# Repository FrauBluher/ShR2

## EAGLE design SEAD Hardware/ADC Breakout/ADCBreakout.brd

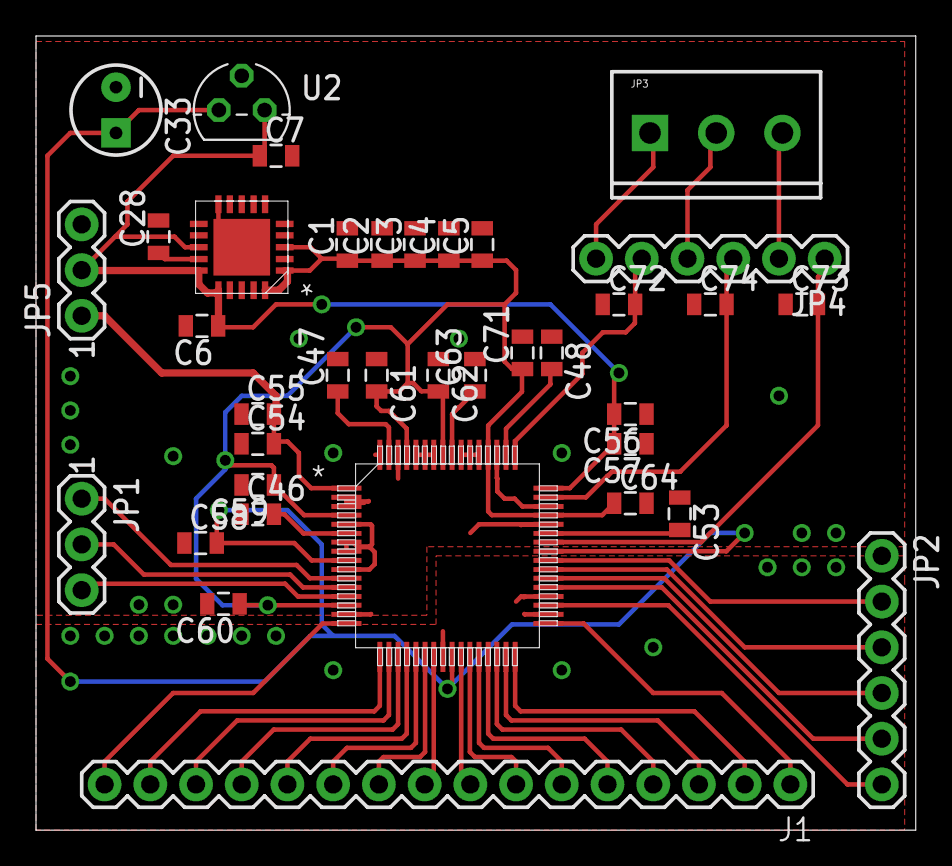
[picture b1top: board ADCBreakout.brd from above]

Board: 2 copper layers, 48.9 x 44.1 mm, 37 parts (0 on the bottom side), 41 nets.

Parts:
C1, C2, C3, C4, C5, C6, C7, C46, C47, C48, C53, C54, C56: 10uF; 0805
C28, C58: 1uF; 0805
C33: 10uF; CPOL-RADIAL-10UF-25V
C55, C57, C59, C60, C61, C62, C64, C71: .1uF; 0805
C63: .47uF; 0805
C72, C73, C74: 10nF; 0805
J1: M16PTH; 1X16
JP1, JP5: M03PTH; 1X03
JP2, JP4: 1X06
JP3: M03SCREW_LOCK; SCREWTERMINAL-3.5MM-3_LOCK.007S
U1: ADS8568_PM_64; PM64
U2: LP2950-3.3ACZ; TO92
U$3: TPS7A4700_RGW_20; RGW20_3P15X3P15

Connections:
AA1_R_OUT: C73.2, JP4.1, U1.42
AA2_R_OUT: C74.2, JP4.3, U1.47
AA3_R_OUT: C72.2, JP4.5, U1.49
ADC_DB0: J1.1, U1.33
ADC_DB1: J1.2, U1.32
ADC_DB2: J1.3, U1.31
ADC_DB3: J1.4, U1.30
ADC_DB4: J1.5, U1.29
ADC_DB5: J1.6, U1.28
ADC_DB6: J1.7, U1.27
ADC_DB7: J1.8, U1.26
ADC_DB8: J1.9, U1.23
ADC_DB9: J1.10, U1.22
ADC_DB10: J1.11, U1.21
ADC_DB11: J1.12, U1.20
ADC_DB12: J1.13, U1.19
ADC_DB13: J1.14, U1.18
ADC_DB14: J1.15, U1.17
ADC_DB15: J1.16, U1.16
BUSY: JP2.6, U1.35
CONV_A: JP2.5, U1.37
CONV_B: JP2.4, U1.38
CONV_C: JP2.3, U1.39
CONV_D: JP2.2, U1.40
CS*: JP1.3, U1.13
GND: C1.2, C2.2, C3.2, C4.2, C5.2, C6.2, C7.2, C28.2, C33.2, C46.1, C47.2, C48.1, C53.1, C54.1, C55.1, C56.1, C57.1, C58.1, C59.2, C60.2, C61.1, C62.1, C63.2, C64.2, C71.2, C72.1, C73.1, C74.1, JP2.1, JP5.3, U1.2, U1.3, U1.5, U1.7, U1.8, U1.10, U1.15, U1.24, U1.34, U1.36, U1.44, U1.46, U1.51, U1.53, U1.54, U1.55, U1.58, U1.59, U1.60, U1.62, U1.64, U2.2, U$3.6, U$3.7, U$3.10, U$3.21
HVDD_12A: C6.1, C7.1, C56.2, C57.2, JP5.2, U1.48, U2.3, U$3.13, U$3.15, U$3.16
HVSS_12A: C54.2, C55.2, JP5.1, U1.1
unnamed: JP3.3, JP4.2
unnamed: JP3.2, JP4.4
unnamed: JP3.1, JP4.6
unnamed: C63.1, U1.56
unnamed: C28.1, U$3.14
unnamed: C46.2, U1.6
unnamed: C53.2, U1.43
unnamed: C48.2, U1.50
unnamed: C47.1, U1.63
RD*: JP1.2, U1.12
VDD3V3_D: C33.1, C58.2, U1.9, U1.25, U1.41, U2.1
VDD5V0_A: C1.1, C2.1, C3.1, C4.1, C5.1, C59.1, C60.1, C61.2, C62.2, C64.1, C71.1, U1.4, U1.14, U1.45, U1.52, U1.57, U1.61, U$3.1, U$3.3, U$3.20
WR*: JP1.1, U1.11

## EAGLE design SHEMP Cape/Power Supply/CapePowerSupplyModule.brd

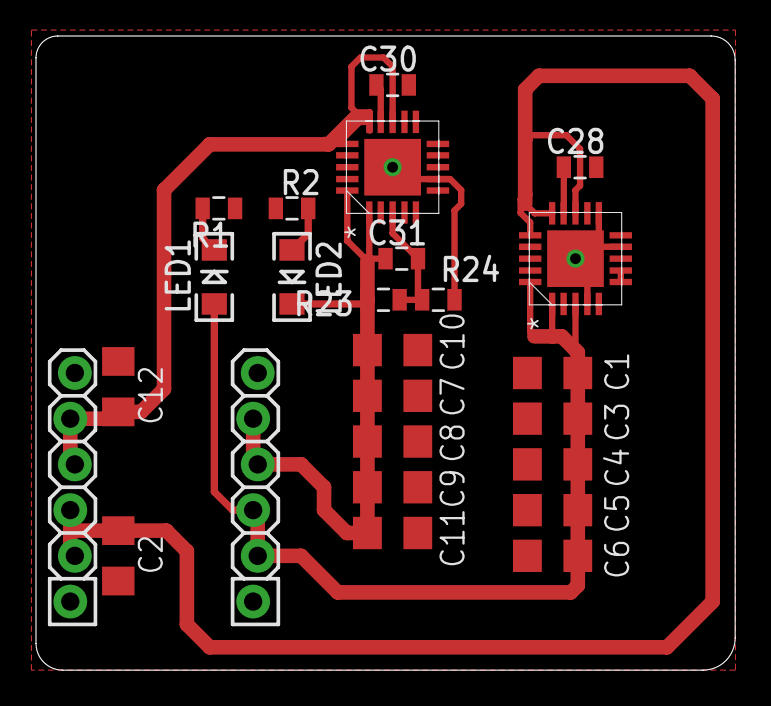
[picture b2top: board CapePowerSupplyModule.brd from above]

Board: 2 copper layers, 38.8 x 35.2 mm, 25 parts (0 on the bottom side), 10 nets.

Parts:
C1, C2, C3, C4, C5, C6, C7, C8, C9, C10, C11, C12: 10uF; 1206
C28, C30: 1uF; 0805
C31: 10nF; 0805
JP1, JP2: 1X06_LOCK
LED1, LED2: LED-1206
R1, R2: 0805
R23: 1.5M; 0805
R24: 162k; 0805
U6: TPS7A3301_RGW_20; RGW20_3P15X3P15
U$3: TPS7A4700_RGW_20; RGW20_3P15X3P15

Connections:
GND: C1.2, C2.2, C3.2, C4.2, C5.2, C6.2, C7.2, C8.2, C9.2, C10.2, C11.2, C12.1, C28.2, C30.2, JP1.1, JP1.6, JP2.1, JP2.6, R1.1, R2.1, R24.1, U6.7, U6.21, U$3.4, U$3.6, U$3.7, U$3.9, U$3.11, U$3.21
HVDD_12A: C1.1, C3.1, C4.1, C5.1, C6.1, JP2.2, JP2.3, LED1.A, U$3.1, U$3.3, U$3.20
HVDD_15D: C2.1, JP1.2, JP1.3, U$3.13, U$3.15, U$3.16
HVSS_12A: C7.1, C8.1, C9.1, C10.1, C11.1, C31.1, JP2.4, JP2.5, LED2.C, R23.2, U6.1, U6.20
HVSS_15D: C12.2, JP1.4, JP1.5, U6.13, U6.15, U6.16
unnamed: LED1.C, R1.2
unnamed: LED2.A, R2.2
unnamed: C31.2, R23.1, R24.2, U6.3
unnamed: C30.1, U6.14
unnamed: C28.1, U$3.14

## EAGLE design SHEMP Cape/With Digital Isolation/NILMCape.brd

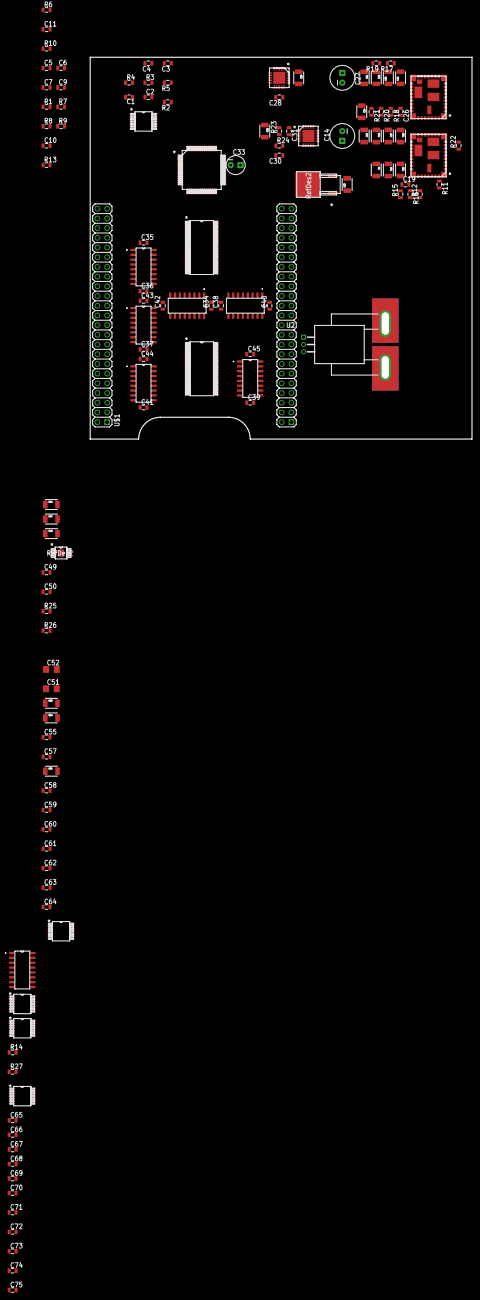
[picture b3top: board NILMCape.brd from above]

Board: 2 copper layers, 100.0 x 100.0 mm, 125 parts (0 on the bottom side), 154 nets, no tracks yet.

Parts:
C1, C2, C3, C4, C5, C6, C7, C9: .33uF; 0805
C8, C12: 4.7uF 50V; 1210
C10, C11, C28, C30, C58: 1uF; 0805
C13, C21, C22, C24: 2.2uF 100V; 1210
C14: 22uF 100V; CPOL-RADIAL-100UF-25V
C15, C16, C17, C18: 22uF 25V; 1210
C19, C26, C31, C49, C50, C72, C73, C74: 10nF; 0805
C20, C23, C25: 22uF; 1210
C27: 27uF 100V; CPOL-RADIAL-100UF-25V
C29, C32: 47uF; 1210
C33: 10uF; CPOL-RADIAL-10UF-25V
C34, C35, C36, C37, C38, C39, C40, C41, C42, C43, C44, C45, C55, C57, C59, C60, C61, C62, C63, C64, C65, C66, C67, C68, C69, C70, C71, C75: .1uF; 0805
C46, C47, C48, C53, C54, C56: 10uF; 1210
C51, C52: 10uF; 1206
R1, R2, R3, R4, R5, R7, R8, R9: 8.2k; 0805
R6, R10, R13: 1k; 0805
R11, R17, R18: 178k; 0805
R12, R14, R21, R22, R27: 0; 0805
R15, R19: 174k; 0805
R16, R20: 15.8k; 0805
R23: 1.5M; 0805
R24: 162k; 0805
R25: 499k; 0805
R26: 154k; 0805
U1: ADS8568_PM_64; PM64
U2: ACS756KCA-050B-PFF-T; 5PFF
U3, U8, U10, U11, U12, U13: SI8663BC-B-IS1; SOIC-16
U4, U14: SN74CBT16390_DGG; DGG56
U5: TPS84250_RKG_41; RKG41
U6: TPS7A3301_RGW_20; RGW20_3P15X3P15
U7: LP2950-33_KVU_3; KVU3
U9: TL074_PW_14; PW14
U15: TPS7A4901_DGN_8; DGN8_1P89X1P57
U16: SI8660BC-B-IS1; SOIC-16
U$1: BEAGLEBONE_OUTLINE; BEAGLEBONE_SHIELD
U$2: TPS84259_RKG_41; RKG41
U$3: TPS7A4700_RGW_20; RGW20_3P15X3P15
U$4, U$5, U$6, U$7: MAX548X; TSSOP14_MC

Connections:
AA1_R_IN: R27.1, U$4.10
AA1_R_OUT: C73.2, U1.42, U$4.11
AA2_R_OUT: C74.2, U1.47, U$5.11
AA3_R_IN: U2.3, U$7.10
AA3_R_OUT: C72.2, U1.49, U$7.11
ADC_DB0: U1.33, U14.1
ADC_DB1: U1.32, U14.54
ADC_DB2: U1.31, U14.4
ADC_DB3: U1.30, U14.51
ADC_DB4: U1.29, U14.7
ADC_DB5: U1.28, U14.48
ADC_DB6: U1.27, U14.10
ADC_DB7: U1.26, U14.45
ADC_DB8: U1.23, U14.15
ADC_DB9: U1.22, U14.40
ADC_DB10: U1.21, U14.18
ADC_DB11: U1.20, U14.37
ADC_DB12: U1.19, U14.21
ADC_DB13: U1.18, U14.34
ADC_DB14: U1.17, U14.24
ADC_DB15: U1.16, U14.31
BBGND: C70.2, U16.8, U$1.1, U$1.2, U$1.47, U$1.48, U$1.89, U$1.90, U$1.91, U$1.92
BBVDD3V3: C70.1, U16.1, U$1.49
BB_DB0: U4.1, U$1.57
BB_DB1: U4.54, U$1.59
BB_DB2: U4.4, U$1.61
BB_DB3: U4.51, U$1.67
BB_DB4: U4.7, U$1.69
BB_DB5: U4.48, U$1.71
BB_DB6: U4.10, U$1.73
BB_DB7: U4.45, U$1.75
BB_DB8: U4.15, U$1.77
BB_DB9: U4.40, U$1.58
BB_DB10: U4.18, U$1.60
BB_DB11: U4.37, U$1.62
BB_DB12: U4.21, U$1.68
BB_DB13: U4.34, U$1.70
BB_DB14: U4.24, U$1.72
BB_DB15: U4.31, U$1.88
GAIN_R_IN: R13.2, R14.1, U9.13, U$6.10
GAIN_R_OUT: R14.2, R27.2, U9.14, U$6.11
GND: C3.1, C4.1, C7.1, C9.1, C19.2, C28.2, C29.2, C30.2, C32.2, C33.2, C35.1, C36.1, C37.1, C38.1, C39.1, C40.1, C41.1, C42.1, C43.1, C45.1, C46.1, C47.2, C48.1, C49.2, C51.2, C52.2, C53.1, C54.1, C55.1, C56.1, C57.1, C58.2, C59.2, C60.2, C61.1, C62.1, C63.2, C64.2, C65.1, C66.1, C67.1, C68.1, C69.1, C71.2, C72.1, C73.1, C74.1, C75.2, R2.2, R5.2, R8.2, R9.2, R12.1, R16.1, R22.1, R24.1, R26.1, U1.2, U1.3, U1.5, U1.7, U1.8, U1.10, U1.15, U1.25, U1.34, U1.36, U1.44, U1.46, U1.51, U1.53, U1.54, U1.55, U1.58, U1.59, U1.60, U1.62, U1.64, U2.1, U3.8, U3.9, U6.7, U6.21, U7.2, U8.8, U8.9, U9.5, U9.12, U10.8, U10.9, U11.8, U11.9, U12.8, U12.9, U13.8, U13.9, U15.4, U15.EPAD, U16.9, U$2.1, U$2.4, U$2.5, U$2.8, U$2.9, U$2.32, U$2.33, U$2.34, U$2.37, U$3.4, U$3.6, U$3.7, U$3.9, U$3.11, U$3.21, U$4.2, U$4.14, U$5.2, U$5.14, U$6.2, U$6.14, U$7.2, U$7.14
HOT_IN: C1.1, R3.2, U2.B1, U2.B2, U2.B3, U2.B4, U2.B5
HOT_TO_LOAD: U2.A1, U2.A2, U2.A3, U2.A4, U2.A5
HVDD_12A: C29.1, C54.2, C55.2, U1.1, U$3.1, U$3.3, U$3.20
HVDD_15D: C20.2, C23.2, C25.2, C52.1, R17.2, U5.10, U5.11, U5.12, U5.13, U5.14, U5.15, U5.39, U7.3, U15.5, U15.8, U$3.13, U$3.15, U$3.16
HVSS_12A: C31.1, C32.1, C56.2, C57.2, R23.2, U1.48, U6.1, U6.20
HVSS_15D: C15.2, C16.2, C17.2, C18.2, U6.13, U6.15, U6.16, U$2.16, U$2.17, U$2.18, U$2.19, U$2.20, U$2.40
unnamed: C5.1, R1.2, R6.2, U9.7
unnamed: C20.1, C21.2, C22.2, C23.1, C24.2, C25.1, C27.2, R21.2, U5.1, U5.4, U5.5, U5.16, U5.17, U5.18, U5.19, U5.20, U5.30, U5.32, U5.33, U5.34, U5.37, U5.40
unnamed: C1.2, C2.1, R2.1, R5.1
unnamed: C3.2, C4.2, R3.1, R4.2
unnamed: R6.1, R10.1, U9.6
unnamed: U16.15, U$4.3
unnamed: C63.1, U1.56
unnamed: C2.2, R4.1, U9.3
unnamed: C5.2, C6.1, R8.1, R9.1
unnamed: C7.2, C9.2, R1.1, R7.2
unnamed: U16.11, U$6.3
unnamed: C6.2, R7.1, U9.10
unnamed: C10.2, U9.8, U9.9
unnamed: C19.1, U$2.28
unnamed: C31.2, R24.2, U6.3
unnamed: R11.1, U$2.36
unnamed: U16.12, U$5.3
unnamed: U16.10, U$7.3
unnamed: U16.14, U$4.4, U$5.4, U$6.4, U$7.4
unnamed: U16.13, U$4.5, U$5.5, U$6.5, U$7.5
unnamed: C10.1, R13.1
unnamed: R12.2, U$2.30
unnamed: C8.2, C12.2, C13.2, C14.2, C15.1, C16.1, C17.1, C18.1, R11.2, R22.2, U$2.10, U$2.11, U$2.12, U$2.13, U$2.14, U$2.15, U$2.39
unnamed: C30.1, U6.14
unnamed: C11.2, R10.2
unnamed: C11.1, U9.1, U9.2
unnamed: R15.1, R16.2, U$2.27
unnamed: R17.1, U5.36
unnamed: R18.2, U5.31
unnamed: R19.1, R20.2, U5.27
unnamed: C26.1, U5.28
unnamed: C26.2, R18.1, R20.1, R21.1, U5.8, U5.9, U5.29
unnamed: C28.1, U$3.14
unnamed: C49.1, U15.6
unnamed: C46.2, U1.6
unnamed: C50.2, R25.1, R26.2, U15.2
unnamed: C53.2, U1.43
unnamed: C48.2, U1.50
unnamed: C47.1, U1.63
R_DB0: U4.56, U12.15
R_DB1: U4.55, U12.14
R_DB2: U4.53, U12.13
R_DB3: U4.52, U11.15
R_DB4: U4.50, U11.14
R_DB5: U4.49, U11.13
R_DB6: U4.47, U10.15
R_DB7: U4.46, U10.14
R_DB8: U4.42, U10.13
R_DB9: U3.15, U4.41
R_DB10: U3.14, U4.39
R_DB11: U3.13, U4.38
R_DB12: U4.36, U8.15
R_DB13: U4.35, U8.14
R_DB14: U4.33, U8.13
R_DB15: U4.32, U13.15
R_DB_ADC0: U12.5, U14.56
R_DB_ADC1: U12.6, U14.55
R_DB_ADC2: U12.7, U14.53
R_DB_ADC3: U11.5, U14.52
R_DB_ADC4: U11.6, U14.50
R_DB_ADC5: U11.7, U14.49
R_DB_ADC6: U10.5, U14.47
R_DB_ADC7: U10.6, U14.46
R_DB_ADC8: U10.7, U14.42
R_DB_ADC9: U3.5, U14.41
R_DB_ADC10: U3.6, U14.39
R_DB_ADC11: U3.7, U14.38
R_DB_ADC12: U8.5, U14.36
R_DB_ADC13: U8.6, U14.35
R_DB_ADC14: U8.7, U14.33
R_DB_ADC15: U13.5, U14.32
VDD3V3_D: C33.1, C34.2, C35.2, C36.2, C37.2, C38.2, C39.2, C40.2, C41.2, C42.2, C43.2, C44.2, C45.2, C58.1, C65.2, C66.2, C67.2, C68.2, C69.2, U1.9, U1.24, U1.41, U3.1, U3.16, U7.1, U8.1, U8.16, U10.1, U10.16, U11.1, U11.16, U12.1, U12.16, U13.1, U13.16, U16.16, U$4.1, U$4.6, U$5.1, U$5.6, U$6.1, U$6.6, U$7.1, U$7.6
VDD5V0_A: C50.1, C51.1, C59.1, C60.1, C61.2, C62.2, C64.1, C71.1, C75.1, R25.2, U1.4, U1.14, U1.45, U1.52, U1.57, U1.61, U2.2, U15.1
VDD_5V: U$1.51, U$1.52
VIN: C8.1, C12.1, C13.1, C14.1, C21.1, C22.1, C24.1, C27.1, R15.2, R19.2, U5.26, U$2.26
W_DB0: U4.2, U12.12
W_DB1: U4.3, U12.11
W_DB2: U4.5, U12.10
W_DB3: U4.6, U11.12
W_DB4: U4.8, U11.11
W_DB5: U4.9, U11.10
W_DB6: U4.11, U10.12
W_DB7: U4.12, U10.11
W_DB8: U4.16, U10.10
W_DB9: U3.12, U4.17
W_DB10: U3.11, U4.19
W_DB11: U3.10, U4.20
W_DB12: U4.22, U8.12
W_DB13: U4.23, U8.11
W_DB14: U4.25, U8.10
W_DB15: U4.26, U13.12
W_DB_ADC0: U12.2, U14.2
W_DB_ADC1: U12.3, U14.3
W_DB_ADC2: U12.4, U14.5
W_DB_ADC3: U11.2, U14.6
W_DB_ADC4: U11.3, U14.8
W_DB_ADC6: U10.2, U11.4, U14.11
W_DB_ADC7: U10.3, U14.12
W_DB_ADC8: U10.4, U14.16
W_DB_ADC9: U3.2, U14.17
W_DB_ADC10: U3.3, U14.19
W_DB_ADC11: U3.4, U14.20
W_DB_ADC12: U8.2, U14.22
W_DB_ADC13: U8.3, U14.23
W_DB_ADC14: U8.4, U14.25
W_DB_ADC15: U13.2, U14.26
